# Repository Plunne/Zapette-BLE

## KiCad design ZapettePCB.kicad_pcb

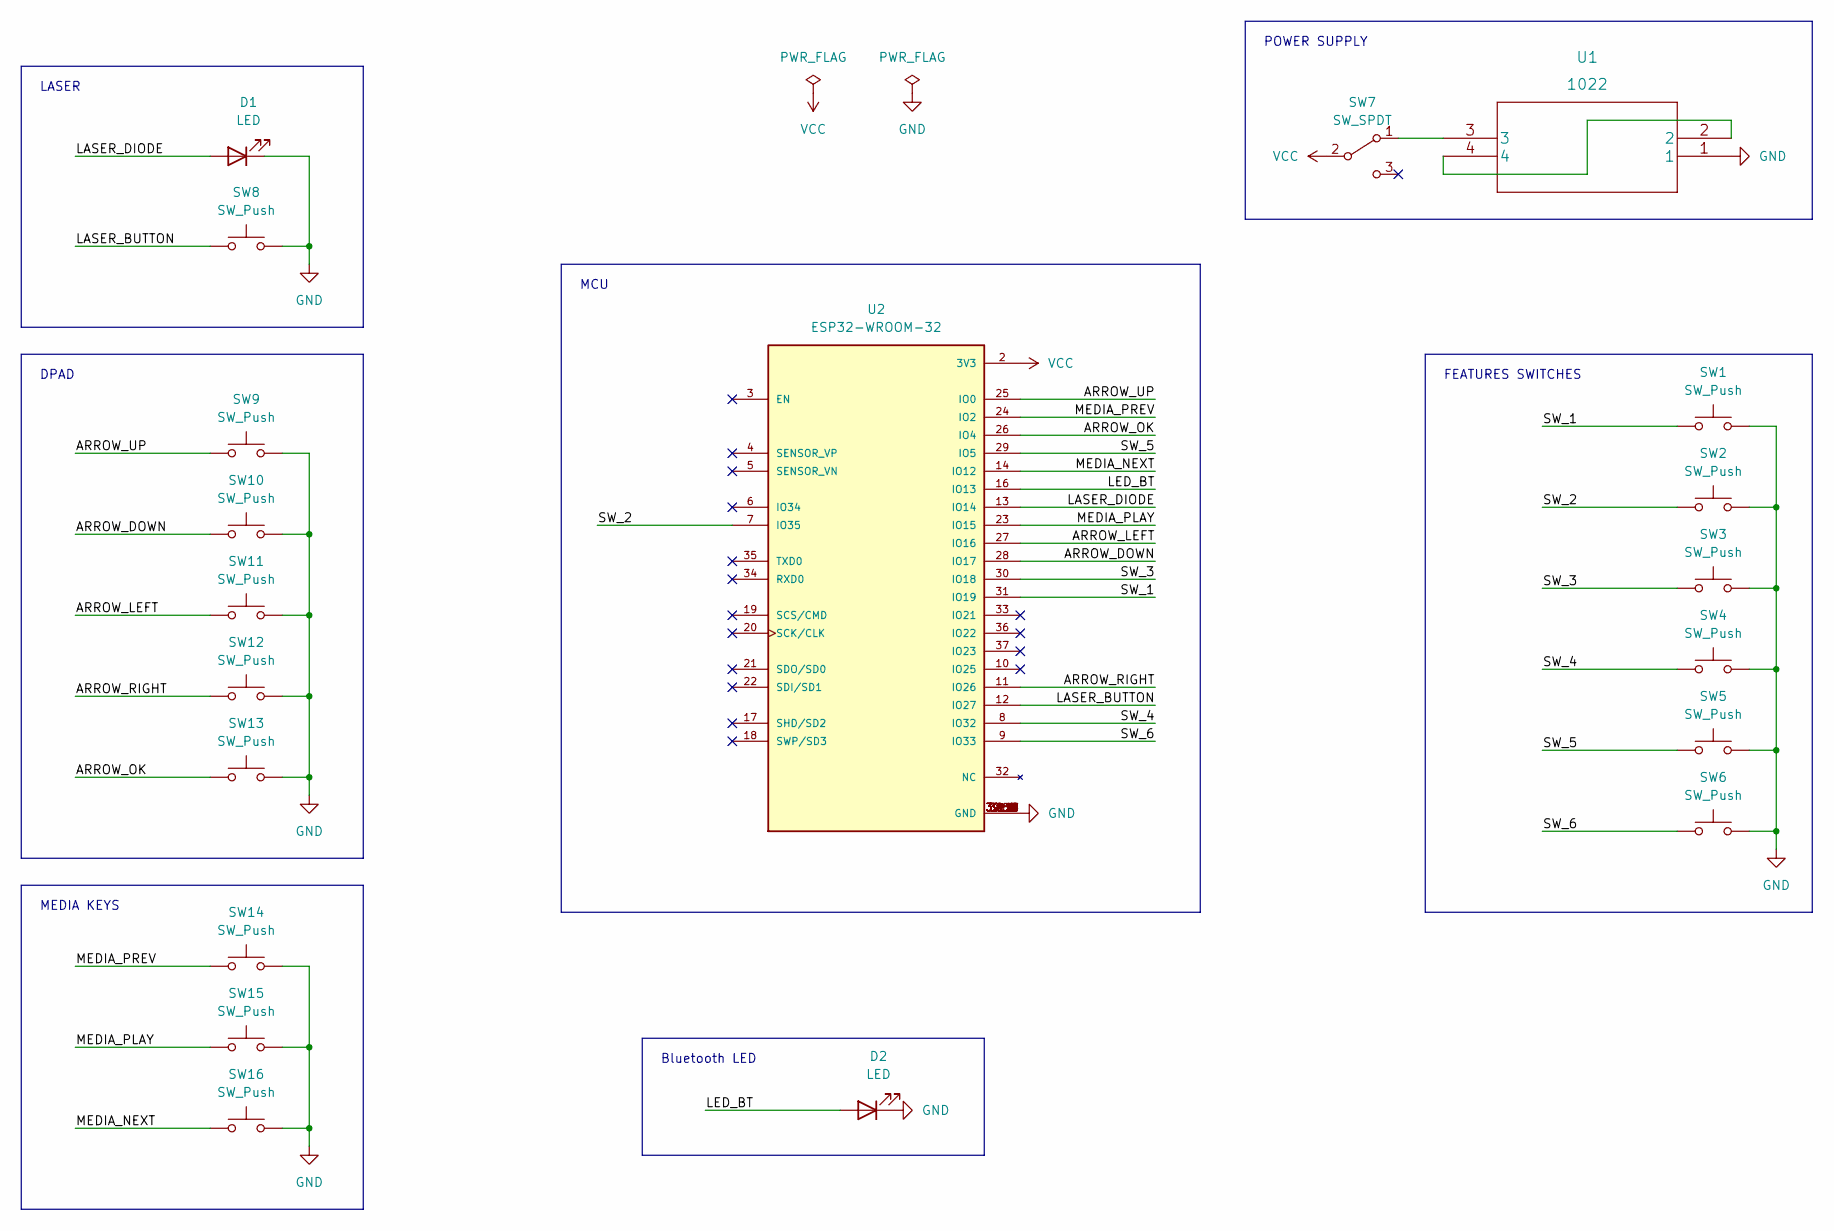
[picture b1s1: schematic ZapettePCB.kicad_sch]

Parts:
D1: LED; LED_1210_3225Metric
D2: LED; LED_0603_1608Metric
SW1, SW2, SW3, SW4, SW5, SW6, SW8, SW9, SW10, SW11, SW12, SW13, SW14, SW15, SW16: SW_Push; SW_Push_1P1T_NO_6x6mm_H9.5mm
SW7: SW_SPDT; SW_Slide_1P2T_CK_OS102011MS2Q
U1: 1022
U2: ESP32-WROOM-32; MODULE_ESP32-WROOM-32; PARTREV 2.9

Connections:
/ARROW_DOWN: SW10.1, U2.28 (IO17)
/ARROW_LEFT: SW11.1, U2.27 (IO16)
/ARROW_OK: SW13.1, U2.26 (IO4)
/ARROW_RIGHT: SW12.1, U2.11 (IO26)
/ARROW_UP: SW9.1, U2.25 (IO0)
/LASER_BUTTON: SW8.1, U2.12 (IO27)
/LASER_DIODE: D1.2 (A), U2.13 (IO14)
/LED_BT: D2.2 (A), U2.16 (IO13)
/MEDIA_NEXT: SW16.1, U2.14 (IO12)
/MEDIA_PLAY: SW15.1, U2.23 (IO15)
/MEDIA_PREV: SW14.1, U2.24 (IO2)
/SW_1: SW1.1, U2.31 (IO19)
/SW_2: SW2.1, U2.7 (IO35)
/SW_3: SW3.1, U2.30 (IO18)
/SW_4: SW4.1, U2.8 (IO32)
/SW_5: SW5.1, U2.29 (IO5)
/SW_6: SW6.1, U2.9 (IO33)
GND: D1.1 (K), D2.1 (K), SW1.2, SW2.2, SW3.2, SW4.2, SW5.2, SW6.2, SW8.2, SW9.2, SW10.2, SW11.2, SW12.2, SW13.2, SW14.2, SW15.2, SW16.2, U1.1, U2.1 (GND), U2.15 (GND), U2.38 (GND), U2.39_1 (GND), U2.39_2 (GND), U2.39_3 (GND), U2.39_4 (GND), U2.39_5 (GND), U2.39_6 (GND), U2.39_7 (GND), U2.39_8 (GND), U2.39_9 (GND), U2.39_10 (GND), U2.39_11 (GND), U2.39_12 (GND), U2.39_13 (GND), U2.39_14 (GND), U2.39_15 (GND), U2.39_16 (GND), U2.39_17 (GND), U2.39_18 (GND), U2.39_19 (GND), U2.39_20 (GND), U2.39_21 (GND)
unnamed: U1.2, U1.4
unnamed: SW7.1 (A), U1.3
VCC: SW7.2 (B), U2.2 (3V3)

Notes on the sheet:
MCU
POWER SUPPLY
DPAD
LASER
Bluetooth LED
MEDIA KEYS
FEATURES SWITCHES

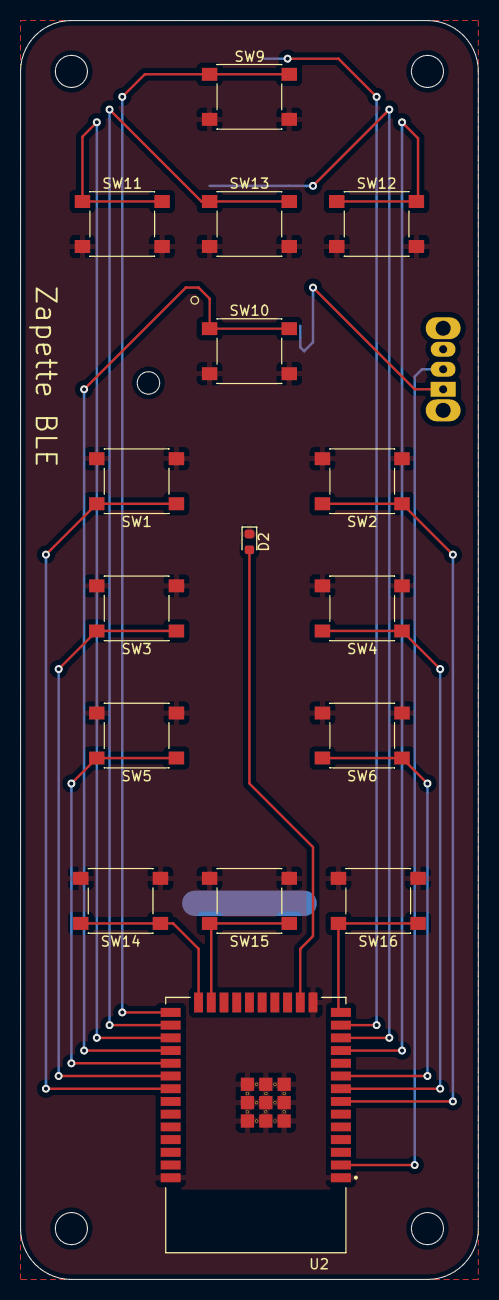
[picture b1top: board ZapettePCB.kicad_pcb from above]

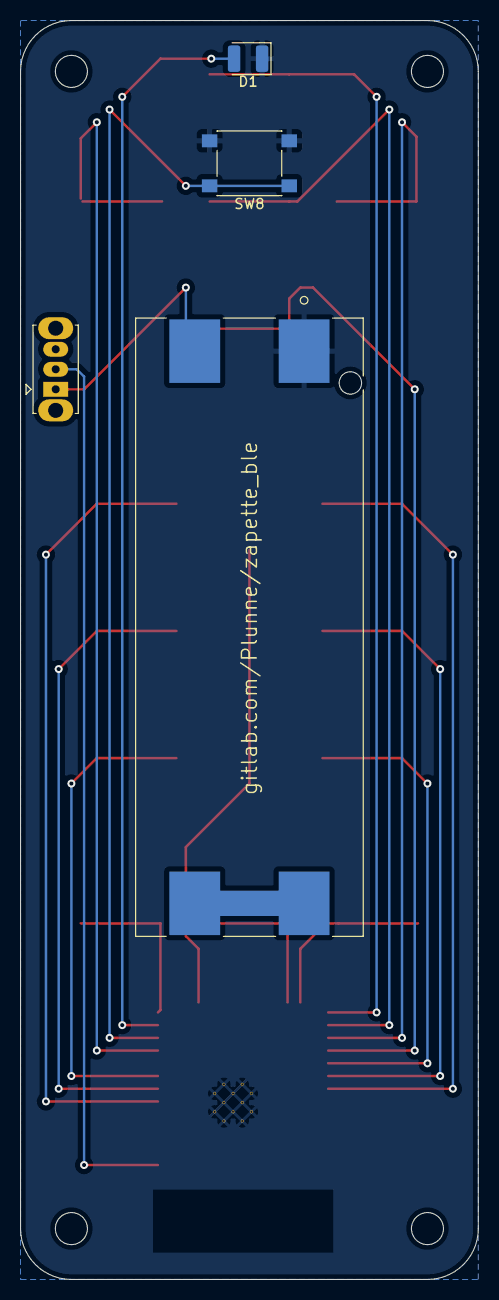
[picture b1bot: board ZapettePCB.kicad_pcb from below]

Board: 2 copper layers, 45.7 x 125.7 mm, 20 parts (4 on the bottom side), 21 nets.

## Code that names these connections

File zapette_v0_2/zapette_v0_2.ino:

/***************************************************************************************
 *
 * ███████╗ █████╗ ██████╗ ███████╗████████╗████████╗███████╗    ██████╗ ██╗     ███████╗
 * ╚══███╔╝██╔══██╗██╔══██╗██╔════╝╚══██╔══╝╚══██╔══╝██╔════╝    ██╔══██╗██║     ██╔════╝
 *   ███╔╝ ███████║██████╔╝█████╗     ██║      ██║   █████╗      ██████╔╝██║     █████╗  
 *  ███╔╝  ██╔══██║██╔═══╝ ██╔══╝     ██║      ██║   ██╔══╝      ██╔══██╗██║     ██╔══╝  
 * ███████╗██║  ██║██║     ███████╗   ██║      ██║   ███████╗    ██████╔╝███████╗███████╗
 * ╚══════╝╚═╝  ╚═╝╚═╝     ╚══════╝   ╚═╝      ╚═╝   ╚══════╝    ╚═════╝ ╚══════╝╚══════╝
 *
 * Repo : https://gitlab.com/Plunne/zapette_ble
 *
 * BleKeyboard by @T-vK : https://github.com/T-vK/ESP32-BLE-Keyboard
 *
 ***************************************************************************************/

#include <BleKeyboard.h>

#define USE_NIMBLE

/* Keys */

// Laser
#define LASER_SW			27

// Media keys
#define MEDIA_PLAY			15

/* Design v0.3
MEDIA_PREV			2 <- pulldown only
MEDIA_NEXT			12 <- pulldown only
*/

#define MEDIA_VOL_UP		19
#define MEDIA_VOL_DOWN		18
#define MEDIA_VOL_MUTE		5

/* Design v0.3
MEDIA_VOL_UP    32
MEDIA_VOL_DOWN    33
MEDIA_VOL_MUTE    25 <- new in replacement of GPIO35 external pullup needed
*/

// Arrow keys
// UP_ARROW			0 <- cannot be used (boot reserved)
#define DOWN_ARROW			17
#define LEFT_ARROW			16
#define RIGHT_ARROW			26
#define OK_RETURN			4

// Switch keys
#define SW_KEY1        32
#define SW_KEY2       33

/* Design v0.3
SW_KEY1				19
SW_KEY2				18
SW_KEY3				5
*/

/* Diodes */
#define LED_BLE 			13
#define LASER_DIODE 		14

/* Zapette object setup */
BleKeyboard Zapette("Zapette BLE", "PlunneCeleste", 100);

/*****************
 *     SETUP     *
 *****************/

void setup() {

	/* Limit F_CPU to reduce Power Consumption */
	setCpuFrequencyMhz(80);

	/* Start BLE */
	Zapette.begin();

	/* INPUTS */
    pinMode(LASER_SW, INPUT_PULLUP);
	
    pinMode(MEDIA_PLAY, INPUT_PULLUP);
    // pinMode(MEDIA_PREV, INPUT);
    // pinMode(MEDIA_NEXT, INPUT);
    pinMode(MEDIA_VOL_UP, INPUT_PULLUP);
    pinMode(MEDIA_VOL_DOWN, INPUT_PULLUP);
    pinMode(MEDIA_VOL_MUTE, INPUT_PULLUP);

	// pinMode(UP_ARROW, INPUT_PULLUP);
    pinMode(DOWN_ARROW, INPUT_PULLUP);
    pinMode(LEFT_ARROW, INPUT_PULLUP);
    pinMode(RIGHT_ARROW, INPUT_PULLUP);
    pinMode(OK_RETURN, INPUT_PULLUP);

	pinMode(SW_KEY1, INPUT_PULLUP);
	pinMode(SW_KEY2, INPUT_PULLUP);
	//pinMode(SW_KEY3, INPUT_PULLUP); // v0.3
	
	/* OUTPUTS */
    pinMode(LED_BLE, OUTPUT);
    pinMode(LASER_DIODE, OUTPUT);
}

/****************
 *     LOOP     *
 ****************/

void loop() {

    if(Zapette.isConnected())
	{
		if(!digitalRead(LASER_SW)) {
			digitalWrite(LASER_DIODE, HIGH);
		} else {
			digitalWrite(LASER_DIODE, LOW);
		}
		/* Media Keys */
       	sendMediaToBLE(MEDIA_PLAY, KEY_MEDIA_PLAY_PAUSE); 
       	// sendMediaPullDownToBLE(MEDIA_PREV, KEY_MEDIA_PREVIOUS_TRACK); 
       	// sendMediaPullDownToBLE(MEDIA_NEXT, KEY_MEDIA_NEXT_TRACK); 
       	sendMediaToBLE(MEDIA_VOL_UP, KEY_MEDIA_VOLUME_UP); 
       	sendMediaToBLE(MEDIA_VOL_DOWN, KEY_MEDIA_VOLUME_DOWN); 
       	sendMediaToBLE(MEDIA_VOL_MUTE, KEY_MEDIA_MUTE); 
		/* Normal Keys */
       	// sendKeyToBLE(UP_ARROW, KEY_UP_ARROW); 
       	sendKeyToBLE(DOWN_ARROW, KEY_DOWN_ARROW); 
       	sendKeyToBLE(LEFT_ARROW, KEY_LEFT_ARROW); 
       	sendKeyToBLE(RIGHT_ARROW, KEY_RIGHT_ARROW); 
       	sendKeyToBLE(OK_RETURN, KEY_RETURN);
		/* Switch keys */
		sendKeyToBLE(SW_KEY1, 'f');
		sendKeyToBLE(SW_KEY2, KEY_F5);
		// sendKeyToBLE(SW_KEY3, KEY_ESC);
		delay(150);
		Zapette.releaseAll();
		digitalWrite(LED_BLE, LOW);  // BLE LED = OFF
		
    }
	else
	{
		/* BLE Disconnected */
		digitalWrite(LED_BLE, HIGH);
		delay(100);
		digitalWrite(LED_BLE, LOW);
		delay(100);
		digitalWrite(LED_BLE, HIGH);
		delay(100);
		digitalWrite(LED_BLE, LOW);
		delay(2500);
	}

	
}

/********************
 *     SEND KEY     *
 *      TO BLE      *
 ********************/

/* Normal Keys */
void sendKeyToBLE(uint8_t pin, uint8_t ascii)
{
	if (!digitalRead(pin)) { 			// Key pressed
		digitalWrite(LED_BLE, HIGH); 	// BLE LED = ON
		Zapette.press(ascii); 			// Send NORMAL key to BLE
	}
}

/* Media keys */
void sendMediaToBLE(uint8_t pin, const MediaKeyReport media)
{
	if (!digitalRead(pin)) { 			// Key pressed
		digitalWrite(LED_BLE, HIGH); 	// BLE LED = ON
		Zapette.press(media); 			// Send MEDIA key to BLE
	}
}

/* Maybe v0.3 */
void sendMediaPullDownToBLE(uint8_t pin, const MediaKeyReport media)
{
	if (digitalRead(pin)) { 			// Key pressed
		digitalWrite(LED_BLE, HIGH); 	// BLE LED = ON
		Zapette.press(media); 			// Send MEDIA key to BLE
	}
}

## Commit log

2022-08-06 Init Zapette-BLE
2022-08-06 Init ZapettePCB
2022-08-26 Zapette v0.21

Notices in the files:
parts and their libraries:
Copyright 2021 Accelerated Designs. All rights reserved.
